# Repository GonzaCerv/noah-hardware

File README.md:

# noah-hardware
This repo contains all the hardware description for the Noah project. Here lies 3D models, electronics PCB and Firmware software of the.

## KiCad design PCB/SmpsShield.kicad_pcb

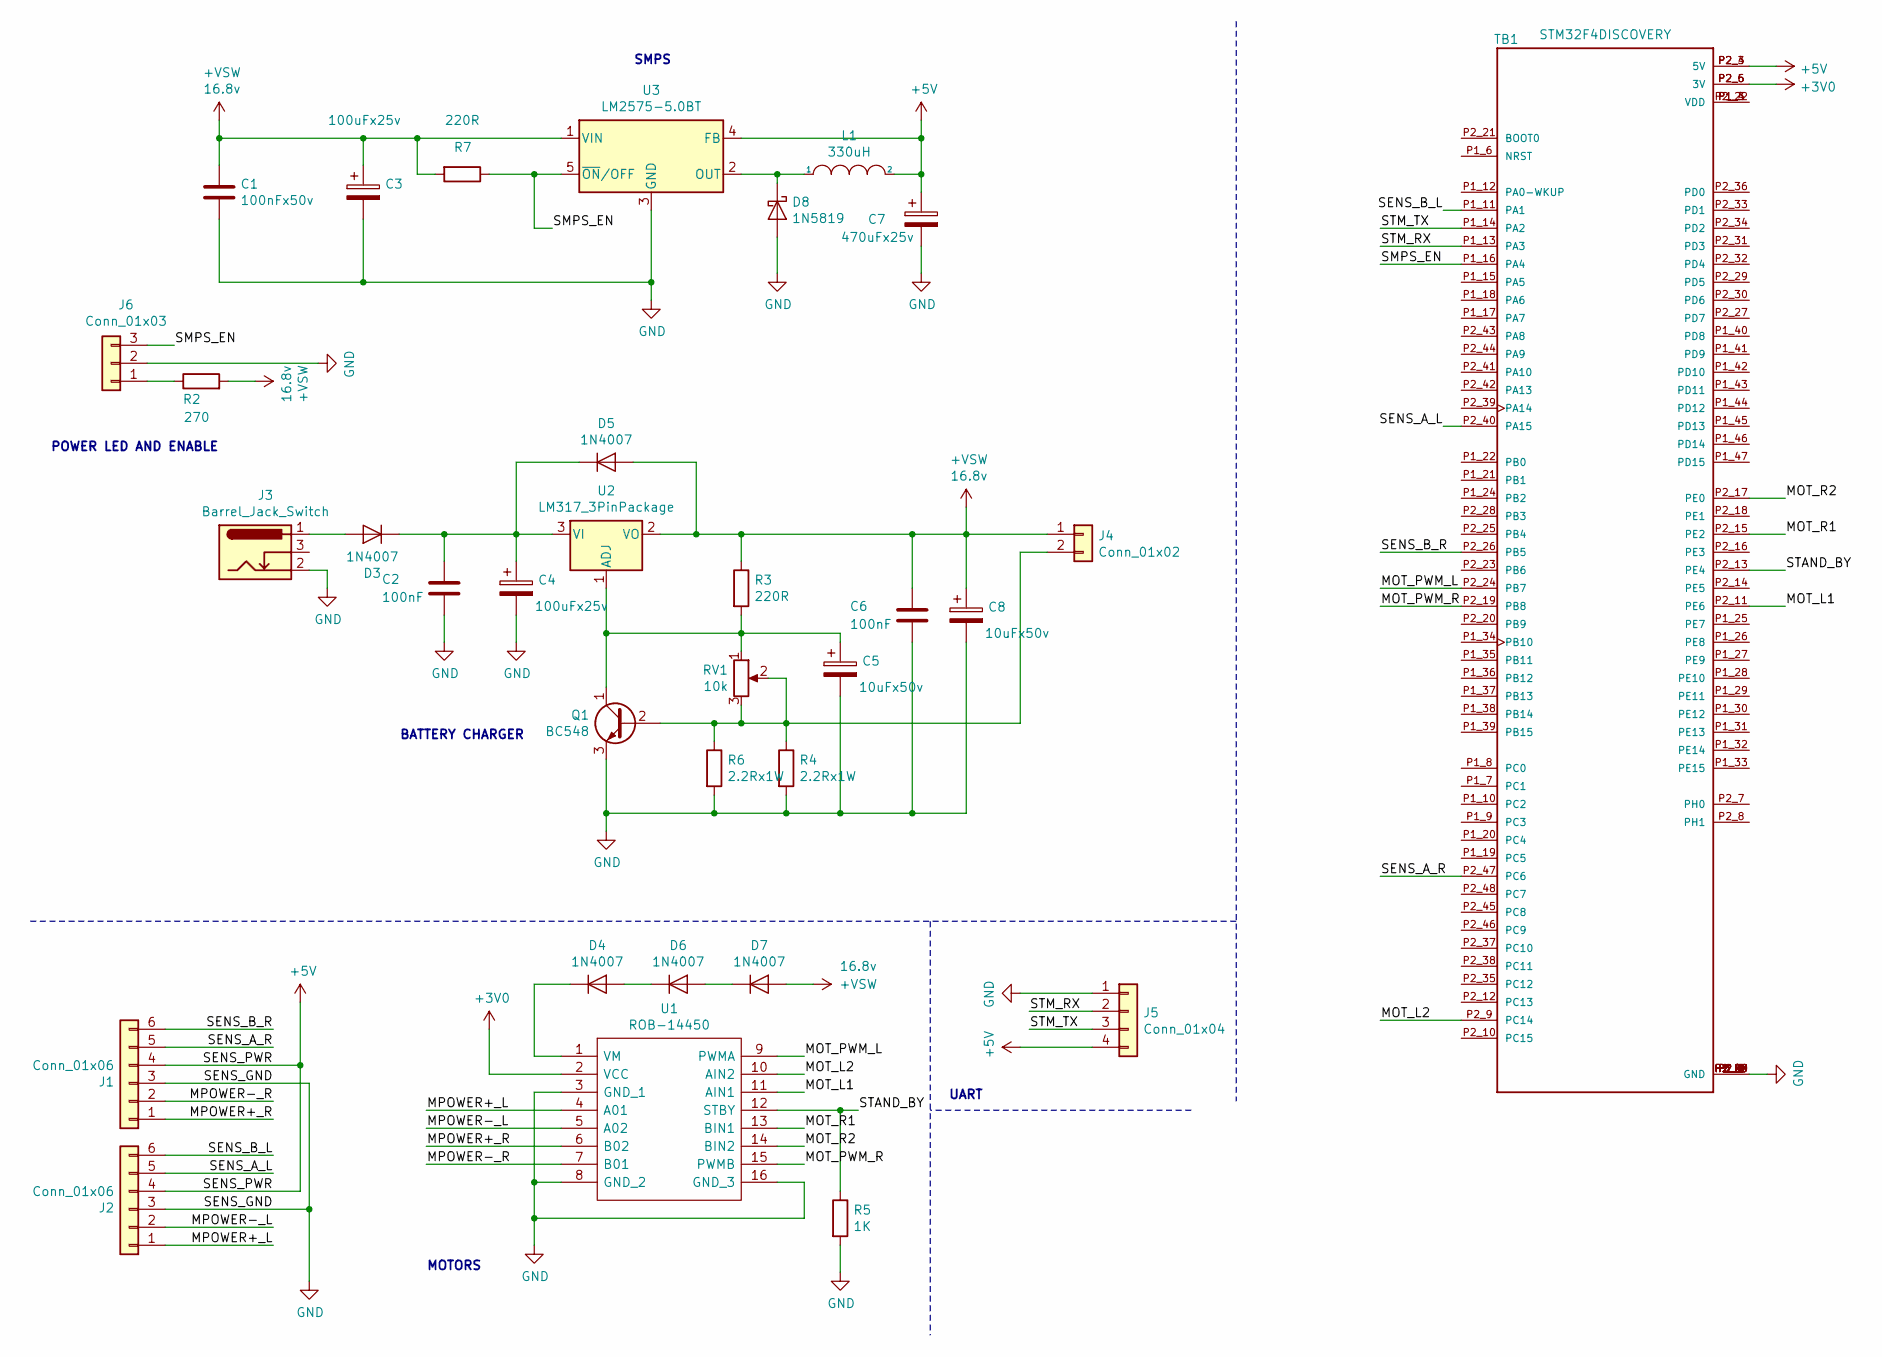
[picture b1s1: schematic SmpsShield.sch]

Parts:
C1: 100nFx50v; C_0805_2012Metric
C2, C6: 100nF; C_0805_2012Metric
C3, C4: 100uFx25v; C_Radial_D6.3mm_H11.0mm_P2.50mm
C5, C8: 10uFx50v; C_Radial_D5.0mm_H11.0mm_P2.00mm
C7: 470uFx25v; C_Radial_D10.0mm_H16.0mm_P5.00mm
D3, D4, D5, D6, D7: 1N4007; D_DO-41_SOD81_P10.16mm_Horizontal
D8: 1N5819; D_DO-41_SOD81_P10.16mm_Horizontal
J1, J2: Conn_01x06; PinHeader_1x06_P2.54mm_Vertical
J3: Barrel_Jack_Switch; BarrelJack_Wuerth_6941xx301002
J4: Conn_01x02; PinHeader_1x02_P2.54mm_Horizontal
J5: Conn_01x04; PinHeader_1x04_P2.54mm_Horizontal
J6: Conn_01x03; PinHeader_1x03_P2.54mm_Vertical
L1: 330uH; L_Radial_D16.8mm_P12.07mm_Vishay_IHB-1
Q1: BC548; TO-92_Inline
R2: 270; R_Axial_DIN0309_L9.0mm_D3.2mm_P5.08mm_Vertical
R3, R7: 220R; R_Axial_DIN0309_L9.0mm_D3.2mm_P12.70mm_Horizontal
R4, R6: 2.2Rx1W; R_Axial_DIN0309_L9.0mm_D3.2mm_P12.70mm_Horizontal
R5: 1K; R_Axial_DIN0309_L9.0mm_D3.2mm_P12.70mm_Horizontal
RV1: 10k; Potentiometer_Bourns_3386F_Vertical
TB1: STM32F4DISCOVERY; MODULE_STM32F4DISCOVERY
U1: ROB-14450; ROB14450; Manufacturer_Part_Number ROB-14450; Mouser Part Number 474-ROB-14450
U2: LM317_3PinPackage; TO-220-3_Horizontal_TabDown
U3: LM2575-5.0BT; TO-220-5_Horizontal_TabDown

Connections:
+3V0: TB1.P2_5 (3V), TB1.P2_6 (3V), U1.2 (VCC)
+5V: C7.1, J1.4, J2.4, J5.4, L1.2, TB1.P2_3 (5V), TB1.P2_4 (5V), U3.4 (FB)
+VSW: C1.1, C3.1, C6.1, C8.1, D5.2 (A), D7.2 (A), J4.1, R2.2, R3.1, R7.2, U2.2 (VO), U3.1 (VIN)
/MOT_L1: TB1.P2_11 (PE6), U1.11 (AIN1)
/MOT_L2: TB1.P2_9 (PC14), U1.10 (AIN2)
/MOT_PWM_L: TB1.P2_24 (PB7), U1.9 (PWMA)
/MOT_PWM_R: TB1.P2_19 (PB8), U1.15 (PWMB)
/MOT_R1: TB1.P2_15 (PE2), U1.13 (BIN1)
/MOT_R2: TB1.P2_17 (PE0), U1.14 (BIN2)
/MPOWER+_L: J2.1, U1.4 (A01)
/MPOWER+_R: J1.1, U1.6 (B02)
/MPOWER-_L: J2.2, U1.5 (A02)
/MPOWER-_R: J1.2, U1.7 (B01)
/SENS_A_L: J2.5, TB1.P2_40 (PA15)
/SENS_A_R: J1.5, TB1.P2_47 (PC6)
/SENS_B_L: J2.6, TB1.P1_11 (PA1)
/SENS_B_R: J1.6, TB1.P2_26 (PB5)
/SMPS_EN: J6.3, R7.1, TB1.P1_16 (PA4), U3.5 (~ON~/OFF)
/STAND_BY: R5.1, TB1.P2_13 (PE4), U1.12 (STBY)
/STM_RX: J5.2, TB1.P1_13 (PA3)
/STM_TX: J5.3, TB1.P1_14 (PA2)
GND: C1.2, C2.2, C3.2, C4.2, C5.2, C6.2, C7.2, C8.2, D8.2 (A), J1.3, J2.3, J3.2, J5.1, J6.2, Q1.3 (E), R4.2, R5.2, R6.2, TB1.P1_1 (GND), TB1.P1_2 (GND), TB1.P1_5 (GND), TB1.P1_23 (GND), TB1.P1_49 (GND), TB1.P1_50 (GND), TB1.P2_1 (GND), TB1.P2_2 (GND), TB1.P2_49 (GND), TB1.P2_50 (GND), U1.3 (GND_1), U1.8 (GND_2), U1.16 (GND_3), U3.3 (GND)
unnamed: C2.1, C4.1, D3.1 (K), D5.1 (K), U2.3 (VI)
unnamed: C5.1, Q1.1 (C), R3.2, RV1.1, U2.1 (ADJ)
unnamed: D3.2 (A), J3.1
unnamed: D4.1 (K), U1.1 (VM)
unnamed: D4.2 (A), D6.1 (K)
unnamed: D6.2 (A), D7.1 (K)
unnamed: D8.1 (K), L1.1, U3.2 (OUT)
unnamed: J4.2, Q1.2 (B), R4.1, R6.1, RV1.2, RV1.3
unnamed: J6.1, R2.1
unnamed: TB1.P1_3 (VDD), TB1.P1_4 (VDD), TB1.P2_22 (VDD)

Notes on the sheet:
POWER LED AND ENABLE
MOTORS
BATTERY CHARGER
SMPS
UART

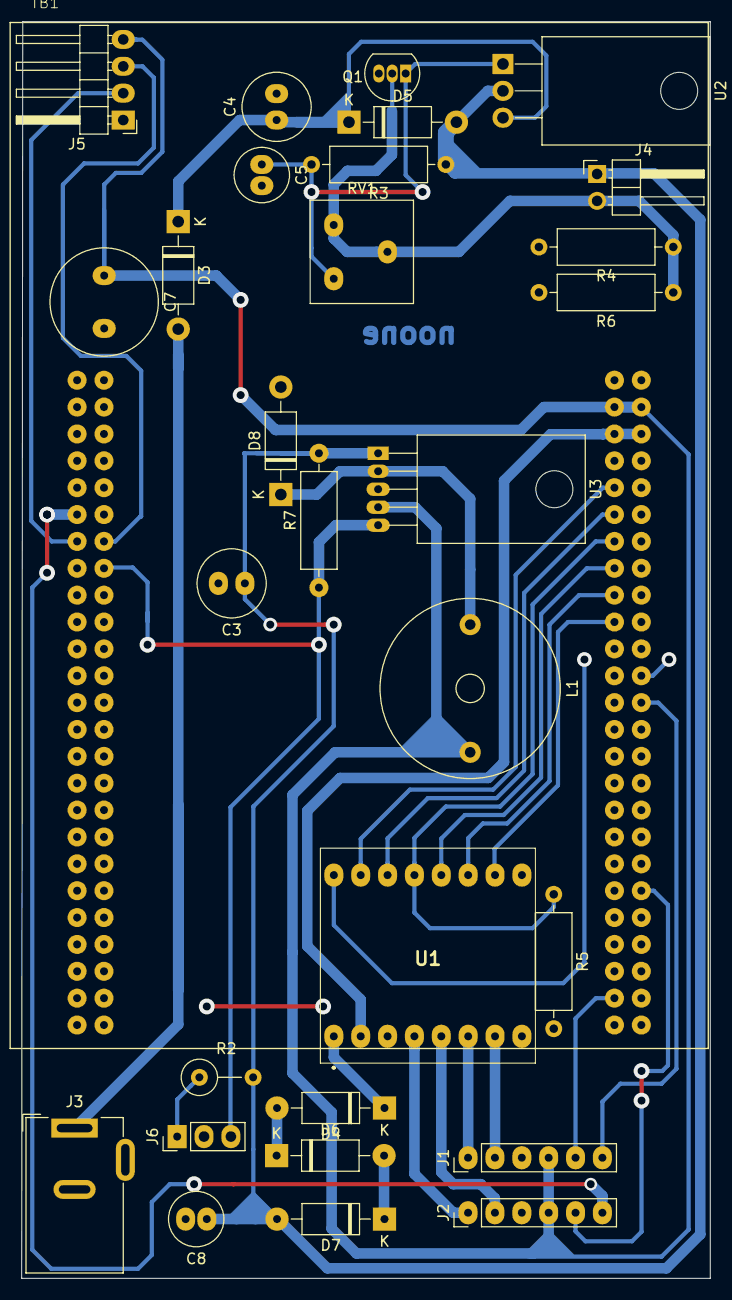
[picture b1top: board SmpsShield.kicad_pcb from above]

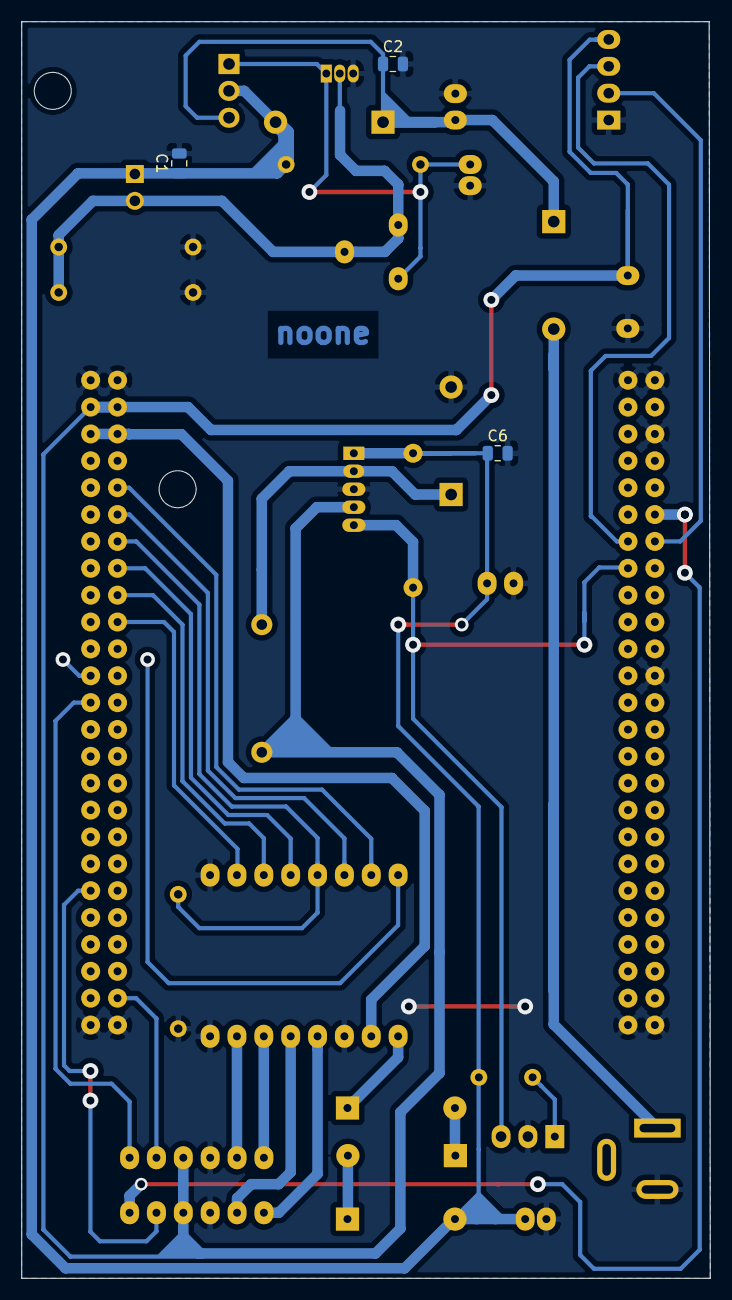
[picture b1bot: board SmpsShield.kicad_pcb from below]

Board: 2 copper layers, 65.1 x 118.8 mm, 33 parts (3 on the bottom side), 32 nets.

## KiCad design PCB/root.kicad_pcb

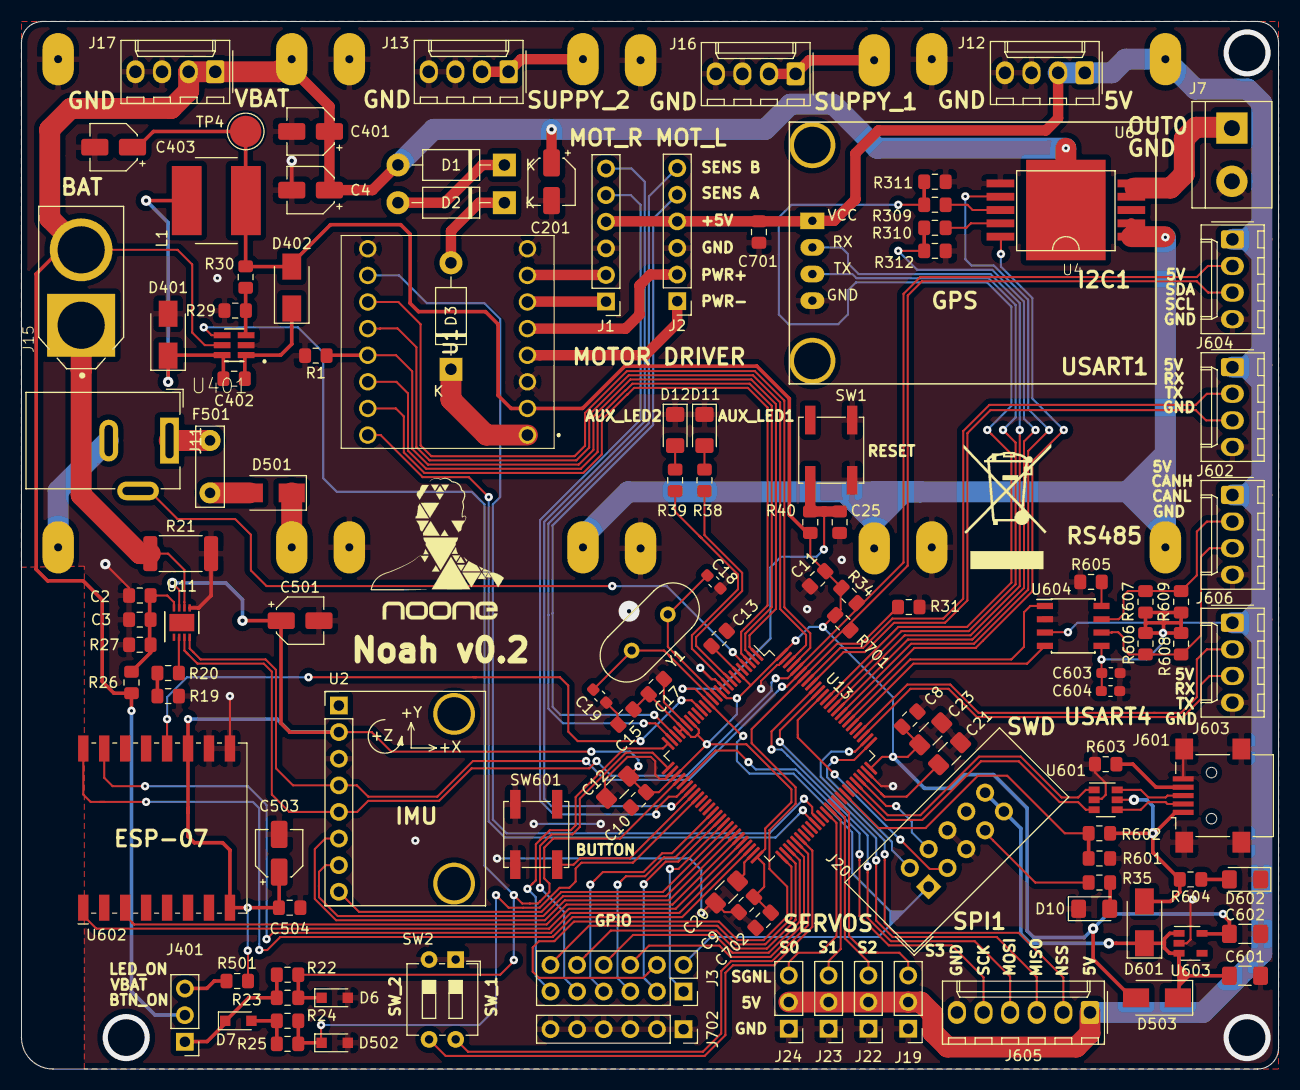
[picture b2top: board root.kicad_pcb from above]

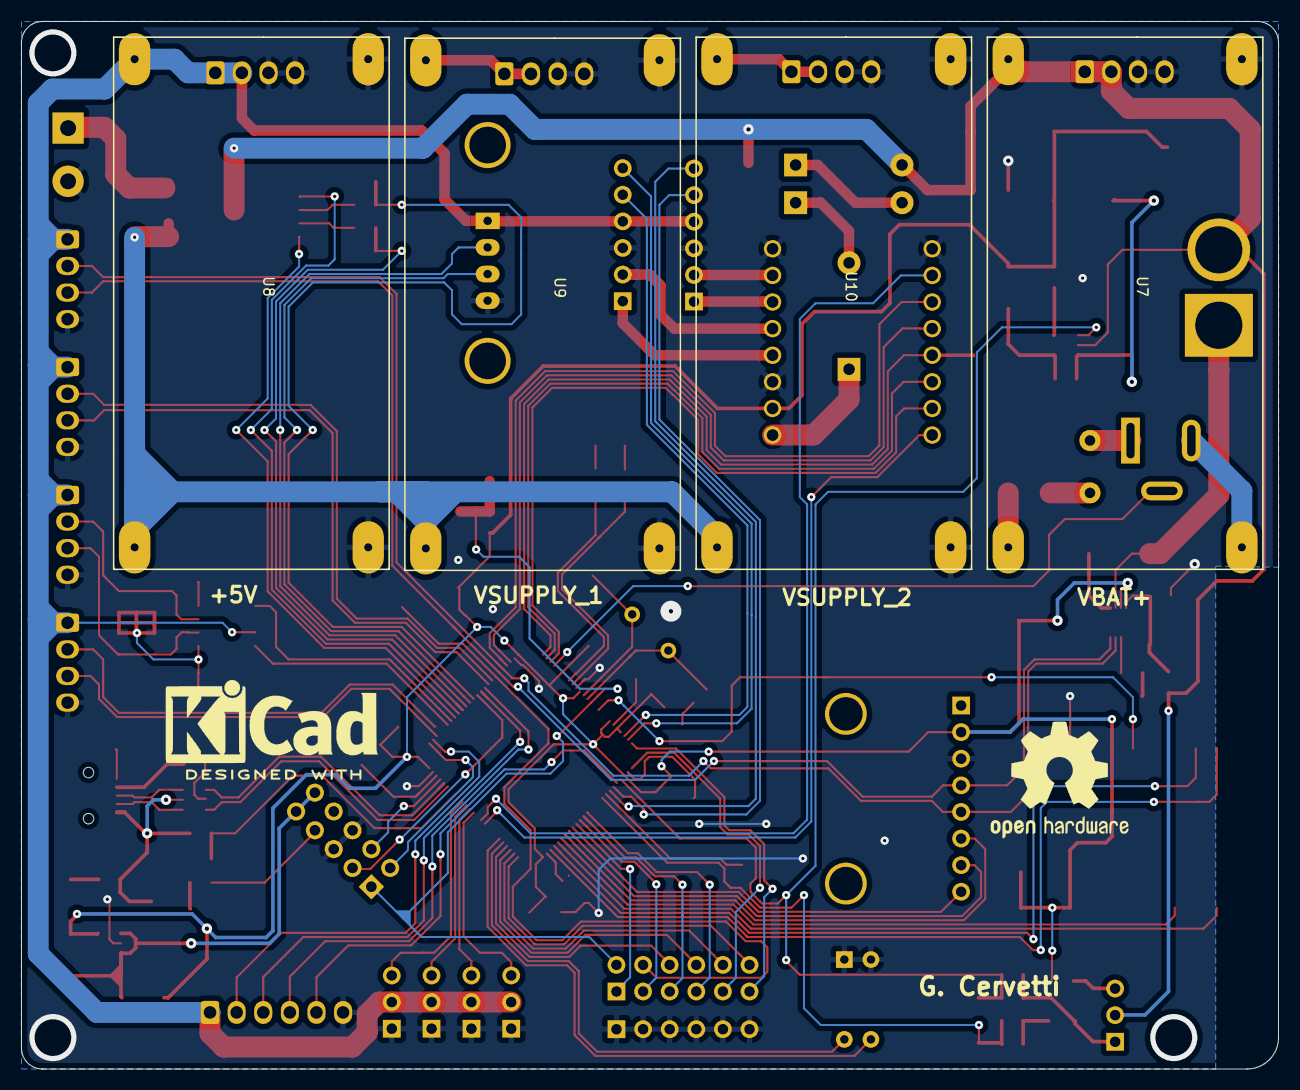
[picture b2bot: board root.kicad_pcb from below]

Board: 2 copper layers, 120.0 x 100.0 mm, 123 parts (4 on the bottom side), 116 nets.

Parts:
C2, C3, C8, C9, C10, C11, C13, C15, C17, C25, C402, C504, C701, C702: 100nF; C_0805_2012Metric_Pad1.15x1.40mm_HandSolder
C4, C201, C401, C403, C501, C503: 10uF; CP_Elec_4x4.5
C12, C20, C21, C23, C601, C602: 2.2uF; C_1206_3216Metric_Pad1.42x1.75mm_HandSolder
C18, C19, C603, C604: 22pF; C_0603_1608Metric_Pad1.05x0.95mm_HandSolder
D1, D2, D3: 1N4007; D_DO-41_SOD81_P10.16mm_Horizontal
D6, D7, D502: MM3Z3V3B; D_SOD-323_HandSoldering
D10, D11, D12, D602: LED; LED_1206_3216Metric_Pad1.42x1.75mm_HandSolder
D401, D402, D501, D503, D601: B140-E3; D_SMA
F501: Polyfuse; C_Disc_D7.5mm_W2.5mm_P5.00mm
J1, J2: Conn_01x06; PinHeader_1x06_P2.54mm_Vertical
J3: Conn_02x06_Odd_Even; PinSocket_2x06_P2.54mm_Vertical
J7: Screw_Terminal_01x02; TerminalBlock_bornier-2_P5.08mm
J11: Barrel_Jack_Switch; BarrelJack_Wuerth_6941xx301002
J12, J13, J16, J17, J602, J603, J604, J606: Conn_01x04; Molex_KK-254_AE-6410-04A_1x04_P2.54mm_Vertical
J15: XT60-M; AMASS_XT60-M
J19, J22, J23, J24, J401: Conn_01x03_Male; PinHeader_1x03_P2.54mm_Vertical
J20: Conn_02x05_Odd_Even; IDC-Header_2x05_P2.54mm_Vertical
J601: USB_B_Mini; USB_Mini-B_Lumberg_2486_01_Horizontal
J605: Conn_01x06; Molex_KK-254_AE-6410-06A_1x06_P2.54mm_Vertical
J702: Conn_01x06; PinSocket_1x06_P2.54mm_Vertical
L1: 22uH; L_Bourns_SRN8040TA
R1, R22, R23, R24, R25, R27, R31, R34, R40, R605, R701: 1K-1%; R_0805_2012Metric_Pad1.15x1.40mm_HandSolder
R19, R20, R603: 100K-0.1%; R_0805_2012Metric_Pad1.15x1.40mm_HandSolder
R21: 0.03Ohm-1%; R_2512_6332Metric
R26, R29: 10K-1%; R_0805_2012Metric_Pad1.15x1.40mm_HandSolder
R30: 31.6K-1%; R_0805_2012Metric_Pad1.15x1.40mm_HandSolder
R35, R38, R39, R501, R604, R606, R607, R608, R609: 120; R_0805_2012Metric_Pad1.15x1.40mm_HandSolder
R309, R310, R602: 5K6; R_0805_2012Metric_Pad1.15x1.40mm_HandSolder
R311, R312, R601: 3K3; R_0805_2012Metric_Pad1.15x1.40mm_HandSolder
SW1, SW601: SW_DPST_x2; SW_SPST_EVPBF
SW2: SW_DIP_x02; SW_DIP_SPSTx02_Slide_6.7x6.64mm_W7.62mm_P2.54mm_LowProfile
TP4: 3v3 Low Power; TestPoint_Pad_D3.0mm
U1: ROB-14450; ROB14450
U2: GY-91
U4: VND830SPTR-E
U6: GY-NEO6MV2
U7, U8, U9, U10: XL4015; XL4015_Converter
U11: STC3100IST; DFN-8-1EP_3x3mm_P0.5mm_EP1.66x2.38mm
U13: STM32F407VGTx; LQFP-100_14x14mm_P0.5mm
U401: MCP16301T-I_CHY; SOT95P270X145-6N
U601: USBLC6-2SC6; SOT-23-6
U602: ESP-07
U603: TLV75533PDBV; SOT-23-5
U604: MCP2551-I-SN; SOIC-8_3.9x4.9mm_P1.27mm
Y1: 8Mhz; Crystal_HC49-U_Vertical

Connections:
5V_ICSP: C601.1, D503.1, D601.1, J20.9, J20.10, U603.1, U603.3
+3V3: C8.2, C9.2, C10.2, C11.2, C12.1, C13.2, C15.2, C17.2, C23.1, C403.1, C501.1, C503.1, C504.1, C602.1, C702.1, D402.2, D503.2, L1.2, R30.2, R34.1, R40.1, R501.2, R701.1, TP4.1, U1.2, U2.2, U11.7, U13.6, U13.11, U13.19, U13.21, U13.22, U13.28, U13.50, U13.75, U13.100, U602.8, U602.11, U603.5
+5V: C701.1, J1.4, J2.4, J12.1, J12.2, J19.2, J22.2, J23.2, J24.2, J602.1, J603.1, J604.1, J605.1, J606.1, U6.1, U8.3, U604.3
+VSW: C4.1, C201.1, C401.1, D1.2, J15.2, J17.1, J17.2, J401.2, R26.2, U4.11, U7.3, U401.5
/MC34063/EN_POWER_3V3: D6.1, R22.2, R23.2, U13.29, U401.4
/Microcontroller/AUX_LED1: R38.2, U13.8
/Microcontroller/AUX_LED2: R39.2, U13.9
/Microcontroller/BOOT0: J3.4, R31.1, U13.94
/Microcontroller/BUTTON: SW601.2, U13.33
/Microcontroller/CAN1_MISO: U13.81, U604.4
/Microcontroller/CAN1_MOSI: U13.82, U604.1
/Microcontroller/CHARGER_CONNECTED: J11.3, U13.4
/Microcontroller/DIP_SW_1: SW2.4, U13.55
/Microcontroller/DIP_SW_2: SW2.3, U13.56
/Microcontroller/ENABLE_PRESSED: D502.1, R24.2, R25.2, U13.34
/Microcontroller/EN_SMPS: U4.10, U13.83
/Microcontroller/ESP07_EN: U13.45, U602.3
/Microcontroller/ESP07_RST: U13.46, U602.1
/Microcontroller/ESP_REGULAR_FLASH: U13.16, U602.12
/Microcontroller/GPIO0: J3.6, U13.54
/Microcontroller/GPIO1: J3.8, U13.53
/Microcontroller/GPIO2: J3.10, U13.52
/Microcontroller/GPIO3: J3.12, U13.51
/Microcontroller/GPIO4: J3.11, U13.25
/Microcontroller/GPIO5: J3.9, U13.26
/Microcontroller/GPIO6: J3.7, U13.38
/Microcontroller/GPIO7: J3.5, U13.39
/Microcontroller/GPIO8: J3.3, U13.40
/Microcontroller/GPIO9: J3.1, U13.41
/Microcontroller/I2C_SCL: J604.3, R701.2, U2.4, U11.4, U13.95
/Microcontroller/I2C_SDA: J604.2, R34.2, U2.5, U11.3, U13.96
/Microcontroller/IMU_NCS: U2.7, U13.43
/Microcontroller/IMU_SDO: U2.6, U13.44
/Microcontroller/MOT_L1: U1.11, U13.2
/Microcontroller/MOT_L2: U1.10, U13.3
/Microcontroller/MOT_PWM_L: U1.9, U13.60
/Microcontroller/MOT_PWM_R: U1.15, U13.61
/Microcontroller/MOT_R1: U1.13, U13.98
/Microcontroller/MOT_R2: U1.14, U13.97
/Microcontroller/MOT_STAND_BY: R1.1, U1.12, U13.1
/Microcontroller/NRST: C25.2, J3.2, J20.1, R40.2, SW1.2, U13.14
/Microcontroller/SENS_A_L: J2.5, U13.23
/Microcontroller/SENS_A_R: J1.5, U13.31
/Microcontroller/SENS_B_L: J2.6, U13.24
/Microcontroller/SENS_B_R: J1.6, U13.32
/Microcontroller/SERVO0: J24.3, U13.63
/Microcontroller/SERVO1: J23.3, U13.64
/Microcontroller/SERVO2: J22.3, U13.65
/Microcontroller/SERVO3: J19.3, U13.66
/Microcontroller/SPI1_MISO: J605.3, U13.90
/Microcontroller/SPI1_MOSI: J605.4, U13.91
/Microcontroller/SPI1_NSS: J605.2, U13.77
/Microcontroller/SPI1_SCK: J605.5, U13.30
/Microcontroller/STATUS_OUT0: R309.2, R311.2, U13.88
/Microcontroller/STATUS_SMPS: R310.2, R312.2, U13.85
/Microcontroller/SWCLK: J20.2, U13.76
/Microcontroller/SWDIO: J20.4, U13.72
/Microcontroller/SWIM: J20.3, U13.89
/Microcontroller/USART1_MISO: J602.2, U13.93
/Microcontroller/USART1_MOSI: J602.3, U13.92
/Microcontroller/USART3_ESP07_MISO: U13.48, U602.16
/Microcontroller/USART3_ESP07_MOSI: U13.47, U602.15
/Microcontroller/USART4_MISO: J603.2, U13.79
/Microcontroller/USART4_MOSI: J603.3, U13.78
/Microcontroller/USB_FS_D+: U13.71, U601.1
/Microcontroller/USB_FS_D-: U13.70, U601.3
/Microcontroller/USB_FS_VBUS: R601.1, R602.2, U13.68
/Motors/MPOWER+_L: J2.1, U1.4
/Motors/MPOWER+_R: J1.1, U1.6
/Motors/MPOWER-_L: J2.2, U1.5
/Motors/MPOWER-_R: J1.2, U1.7
/Peripheral2/CAN+: J606.2, R607.2, R609.2, U604.7
/Peripheral2/CAN-: J606.3, R606.2, R608.2, U604.6
/Peripheral2/USB_CONN+: J601.3, U601.6
/Peripheral2/USB_CONN-: J601.2, U601.4
/Peripheral/CSB: U2.8, U13.42
/Peripheral/EN_OUT0: U4.7, U13.84
/Peripheral/OUT0: J7.1, U4.4, U4.5
/Peripheral/SENSE0: R309.1, U4.8
/Peripheral/SENSE_SMPS: R310.1, U4.9
/Peripheral/SMPS_PWR: U4.1, U4.2, U8.1, U9.1, U10.1
/Peripheral/USART2_GPS_MISO: U6.3, U13.87
/Peripheral/USART2_GPS_MOSI: U6.2, U13.86
/Supply/BTN_ON: D7.1, J401.1, R22.1, R23.1
GND: C2.2, C3.2, C4.2, C8.1, C9.1, C10.1, C11.1, C12.2, C13.1, C15.1, C17.1, C18.2, C19.2, C20.2, C21.2, C23.2, C25.1, C201.2, C401.2, C403.2, C501.2, C503.2, C504.2, C601.2, C602.2, C603.1, C604.1, C701.2, C702.2, D6.2, D10.1, D11.1, D12.1, D401.2, D502.2, D602.1, J1.3, J2.3, J7.2, J12.3, J12.4, J13.3, J13.4, J16.3, J16.4, J17.3, J17.4, J19.1, J20.5, J20.6, J22.1, J23.1, J24.1, J601.5, J601.6, J602.4, J603.4, J604.4, J605.6, J606.4, J702.1, J702.2, J702.3, J702.4, J702.5, J702.6, R1.2, R19.1, R21.2, R27.1, R29.2, R31.2, R311.1, R312.1, R601.2, R603.1, R605.1, SW1.1, SW2.1, SW2.2, SW601.1, U1.3, U1.8, U1.16, U2.3, U4.6, U6.4, U7.4, U8.2, U8.4, U9.2, U9.4, U10.2, U10.4, U11.5, U13.10, U13.20, U13.27, U13.74, U13.99, U401.2, U601.2, U602.9, U602.10, U603.2, U604.2
unnamed: C2.1, C3.1, R26.1, R27.2, U11.8
unnamed: C18.1, U13.12, Y1.1
unnamed: C19.1, U13.13, Y1.2
unnamed: C20.1, U13.49
unnamed: C21.1, U13.73
unnamed: C402.1, D401.1, L1.1, U401.6
unnamed: C402.2, D402.1, U401.1
unnamed: C603.2, C604.2, R606.1, R607.1, R608.1, R609.1, U604.5
unnamed: D1.1, D2.2
unnamed: D2.1, D3.2
unnamed: D3.1, U1.1
unnamed: D7.2, R24.1, R25.1
unnamed: D10.2, R35.1
unnamed: D11.2, R38.1
unnamed: D12.2, R39.1
unnamed: D501.1, U7.1
unnamed: D501.2, F501.1
unnamed: D601.2, J601.1, R602.1, R604.2, U601.5
unnamed: D602.2, R604.1
unnamed: F501.2, J11.1
unnamed: J11.2, U7.2
unnamed: J15.1, R21.1, U11.6
unnamed: J20.7, R35.2
unnamed: J401.3, R501.1
unnamed: J601.4, R603.2
unnamed: R19.2, R20.2
unnamed: R20.1, U11.2
unnamed: R29.1, R30.1, U401.3
unnamed: R605.2, U604.8
VSUPPLY_1: J16.1, J16.2, U9.3
VSUPPLY_2: J13.1, J13.2, U10.3

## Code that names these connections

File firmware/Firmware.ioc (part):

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Mcu.Name=STM32F407V(E-G)Tx
Mcu.Package=LQFP100
Mcu.UserName=STM32F407VGTx
PA0-WKUP.GPIOParameters=GPIO_Label
PA0-WKUP.GPIO_Label=SENS_A_L
PA0-WKUP.Signal=S_TIM2_CH1_ETR
PA1.GPIOParameters=GPIO_Label
PA1.GPIO_Label=SENS_B_L
PA1.Signal=S_TIM2_CH2
PA11.Mode=Device_Only
PA11.Signal=USB_OTG_FS_DM
PA12.Mode=Device_Only
PA12.Signal=USB_OTG_FS_DP
PA13.Mode=Trace_Asynchronous_SW
PA13.Signal=SYS_JTMS-SWDIO
PA14.Mode=Trace_Asynchronous_SW
PA14.Signal=SYS_JTCK-SWCLK
PA15.Mode=NSS_Signal_Hard_Output
PA15.Signal=SPI1_NSS
PA2.GPIOParameters=GPIO_Label
PA2.GPIO_Label=GPIO4
PA2.Signal=GPIO_Output
PA3.GPIOParameters=GPIO_Label
PA3.GPIO_Label=GPIO5
PA3.Signal=GPIO_Output
PA4.GPIOParameters=GPIO_Label
PA4.GPIO_Label=EN_POWER_3V3
PA4.Signal=GPIO_Input
PA5.Mode=Full_Duplex_Master
PA5.Signal=SPI1_SCK
PA6.GPIOParameters=GPIO_Label
PA6.GPIO_Label=SENS_A_R
PA6.Signal=S_TIM3_CH1
PA7.GPIOParameters=GPIO_Label
PA7.GPIO_Label=SENS_B_R
PA7.Signal=S_TIM3_CH2
PA9.Mode=Activate_VBUS
PA9.Signal=USB_OTG_FS_VBUS
PB10.GPIOParameters=GPIO_Label
PB10.GPIO_Label=USART3_ESP07_MOSI
PB10.Mode=Asynchronous
PB10.Signal=USART3_TX
PB11.GPIOParameters=GPIO_Label
PB11.GPIO_Label=USART3_ESP07_MISO
PB11.Mode=Asynchronous
PB11.Signal=USART3_RX
PB12.GPIOParameters=GPIO_Label
PB12.GPIO_Label=GPIO3
PB12.Signal=GPIO_Output
PB13.GPIOParameters=GPIO_Label
PB13.GPIO_Label=GPIO2
PB13.Signal=GPIO_Output
PB14.GPIOParameters=GPIO_Label
PB14.GPIO_Label=GPIO1
PB14.Signal=GPIO_Output
PB15.GPIOParameters=GPIO_Label
PB15.GPIO_Label=GPIO0
PB15.Signal=GPIO_Output
PB3.Mode=Trace_Asynchronous_SW
PB3.Signal=SYS_JTDO-SWO
PB4.Mode=Full_Duplex_Master
PB4.Signal=SPI1_MISO
PB5.Mode=Full_Duplex_Master
PB5.Signal=SPI1_MOSI
PB6.GPIOParameters=GPIO_Label
PB6.GPIO_Label=USART1_MOSI
PB6.Mode=Asynchronous
PB6.Signal=USART1_TX
PB7.GPIOParameters=GPIO_Label
PB7.GPIO_Label=USART1_MISO
PB7.Mode=Asynchronous
PB7.Signal=USART1_RX
PB8.Mode=I2C
PB8.Signal=I2C1_SCL
PB9.Mode=I2C
PB9.Signal=I2C1_SDA
PC1.GPIOParameters=PinState,GPIO_Label
PC1.GPIO_Label=ESP_REGULAR_FLASH
PC1.PinState=GPIO_PIN_SET
PC1.Signal=GPIO_Output
PC10.GPIOParameters=GPIO_Label
PC10.GPIO_Label=USART4_MOSI
PC10.Mode=Asynchronous
PC10.Signal=UART4_TX
PC11.GPIOParameters=GPIO_Label
PC11.GPIO_Label=USART4_MISO
PC11.Mode=Asynchronous
PC11.Signal=UART4_RX
PC14-OSC32_IN.GPIOParameters=GPIO_Label
PC14-OSC32_IN.GPIO_Label=AUX_LED1
PC14-OSC32_IN.Signal=GPIO_Output
PC15-OSC32_OUT.GPIOParameters=GPIO_Label
PC15-OSC32_OUT.GPIO_Label=AUX_LED2
PC15-OSC32_OUT.Signal=GPIO_Output
PC4.GPIOParameters=GPIO_PuPd,GPIO_Label
PC4.GPIO_Label=BUTTON
PC4.GPIO_PuPd=GPIO_PULLUP
PC4.Signal=GPIO_Input
PC5.GPIOParameters=GPIO_PuPd,GPIO_Label
PC5.GPIO_Label=ENABLE_PRESSED
PC5.GPIO_PuPd=GPIO_PULLDOWN
PC5.Signal=GPIO_Input
PC6.GPIOParameters=GPIO_Label
PC6.GPIO_Label=SERVO0
PC6.Signal=S_TIM8_CH1
PC7.GPIOParameters=GPIO_Label
PC7.GPIO_Label=SERVO1
PC7.Signal=S_TIM8_CH2
PC8.GPIOParameters=GPIO_Label
PC8.GPIO_Label=SERVO2
PC8.Signal=S_TIM8_CH3
PC9.GPIOParameters=GPIO_Label
PC9.GPIO_Label=SERVO3
PC9.Signal=S_TIM8_CH4
PD0.GPIOParameters=GPIO_Label
PD0.GPIO_Label=CAN1_MISO
PD0.Mode=Master
PD0.Signal=CAN1_RX
PD1.GPIOParameters=GPIO_Label
PD1.GPIO_Label=CAN1_MOSI
PD1.Mode=Master
PD1.Signal=CAN1_TX
PD13.GPIOParameters=GPIO_Label
PD13.GPIO_Label=MOT_PWM_L
PD13.Signal=S_TIM4_CH2
PD14.GPIOParameters=GPIO_Label
PD14.GPIO_Label=MOT_PWM_R
PD14.Signal=S_TIM4_CH3
PD2.GPIOParameters=GPIO_Label
PD2.GPIO_Label=EN_SMPS
PD2.Signal=GPIO_Output
PD3.GPIOParameters=GPIO_Label
PD3.GPIO_Label=OUT0
PD3.Signal=GPIO_Output
PD4.GPIOParameters=GPIO_Label
PD4.GPIO_Label=STATUS_SMPS
PD4.Signal=GPIO_Input
PD5.GPIOParameters=GPIO_Label
PD5.GPIO_Label=USART2_GPS_MOSI
PD5.Mode=Asynchronous
PD5.Signal=USART2_TX
PD6.GPIOParameters=GPIO_Label
PD6.GPIO_Label=USART2_GPS_MISO
PD6.Mode=Asynchronous
PD6.Signal=USART2_RX
PD7.GPIOParameters=GPIO_Label
PD7.GPIO_Label=STATUS_OUT0
PD7.Signal=GPIO_Input
PD8.GPIOParameters=GPIO_PuPd,GPIO_Label
PD8.GPIO_Label=DIP_SW_1
PD8.GPIO_PuPd=GPIO_PULLUP
PD8.Signal=GPIO_Input
PD9.GPIOParameters=GPIO_PuPd,GPIO_Label
PD9.GPIO_Label=DIP_SW_2
PD9.GPIO_PuPd=GPIO_PULLUP
PD9.Signal=GPIO_Input
PE0.GPIOParameters=GPIO_Label
PE0.GPIO_Label=MOT_R1
PE0.Signal=GPIO_Output
PE1.GPIOParameters=GPIO_Label
PE1.GPIO_Label=MOT_R2
PE1.Signal=GPIO_Output
PE10.GPIOParameters=GPIO_Label
PE10.GPIO_Label=GPIO9
PE10.Signal=GPIO_Output
PE11.GPIOParameters=GPIO_Label
PE11.GPIO_Label=IMU_CSB
PE11.Signal=GPIO_Output
PE12.GPIOParameters=GPIO_Label
PE12.GPIO_Label=IMU_NCS
PE12.Signal=GPIO_Output
PE13.GPIOParameters=GPIO_Label
PE13.GPIO_Label=IMU_SDO
PE13.Signal=GPIO_Input
PE14.GPIOParameters=GPIO_Label
PE14.GPIO_Label=ESP07_EN
PE14.Signal=GPIO_Output
PE15.GPIOParameters=PinState,GPIO_Label
PE15.GPIO_Label=ESP07_RST
PE15.PinState=GPIO_PIN_RESET
PE15.Signal=GPIO_Output
PE2.GPIOParameters=GPIO_Label
PE2.GPIO_Label=MOT_STAND_BY
PE2.Signal=GPIO_Output
PE3.GPIOParameters=GPIO_Label
PE3.GPIO_Label=MOT_L1
PE3.Signal=GPIO_Output
PE4.GPIOParameters=GPIO_Label
PE4.GPIO_Label=MOT_L2
PE4.Signal=GPIO_Output
PE5.GPIOParameters=GPIO_PuPd,GPIO_Label
PE5.GPIO_Label=CHARGER_CONNECTED
PE5.GPIO_PuPd=GPIO_PULLUP
PE5.Signal=GPIO_Input
PE7.GPIOParameters=GPIO_Label
PE7.GPIO_Label=GPIO6
PE7.Signal=GPIO_Output
PE8.GPIOParameters=GPIO_Label
PE8.GPIO_Label=GPIO7
PE8.Signal=GPIO_Output
PE9.GPIOParameters=GPIO_Label
PE9.GPIO_Label=GPIO8
PE9.Signal=GPIO_Output
PH0-OSC_IN.Mode=HSE-External-Oscillator
PH0-OSC_IN.Signal=RCC_OSC_IN
PH1-OSC_OUT.Mode=HSE-External-Oscillator
PH1-OSC_OUT.Signal=RCC_OSC_OUT
RCC.HSE_VALUE=8000000
RCC.SYSCLKFreq_VALUE=72000000
RCC.SYSCLKSource=RCC_SYSCLKSOURCE_PLLCLK
board=custom

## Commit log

2020-05-14 0.1.0 release
2020-06-30 0.2.0_release
2020-07-20 Refactor Firmware and implement serial communication
2020-07-20 fixup! Refactor Firmware and implement serial communication
2020-07-20 add ROS communications
2020-07-21 Refactor ROSComms checking method for information in package
2020-07-24 Enable usart pullup
2020-08-07 Refactor case for v0.2.0
2020-08-07 Change left motor direction
2020-09-15 add STL for mdf parts
2020-09-15 added STL for printed wheels
2020-09-16 Fix readme
2020-09-16 Fix images
2020-10-05 Add mechanical manual
2020-10-18 Add generic design
2021-02-06 Reorganize firmware code
2021-02-06 Add images to readme
2021-03-06 Add Support for MPU9250
2021-03-13 Add support for IMU
2021-03-16 Update license to MIT
2021-04-27 Prueba rama
2021-04-27 Add BOM to the project #16
2021-05-04 Remove BOM
2021-05-07 Add CONTRIBUTING.md
2021-05-18 Add BOM to project
2021-06-17 Generate STL for 3D printed wheels
